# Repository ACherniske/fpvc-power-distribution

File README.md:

# FPVC Power Distribution Board

A 2-layer power distribution board designed in KiCad for the NFPA Fluid Powered Vehicle Challenge. Handles input fusing, load switching via MOSFETs, and regulated 5V/12V/24V outputs.

---

## Board Images

### Top and bottom layers

| Top layer | Bottom layer |
|---|---|
|  |  |

### Schematic

---

## Ordering from JLCPCB

### 1. Download the Gerber files

Download the latest Gerber files from the [Releases](../../releases) page as a `.zip` file. Do not unzip it — JLCPCB accepts the zip directly.

### 2. Upload to JLCPCB

1. Go to [jlcpcb.com](https://jlcpcb.com) and click **Order Now**
2. Click **Add Gerber File** and upload the `.zip`
3. JLCPCB will render a preview of the board — verify it looks correct before continuing

### 3. Configure the order options

Once uploaded, a list of fabrication options will appear. Set them as follows:

| Option | Value | Notes |
|---|---|---|
| **Base Material** | FR-4 | Standard PCB material |
| **Layers** | 2 | |
| **Dimensions** | Auto-detected | Verify against preview |
| **PCB Qty** | 5 (minimum) | Adjust as needed |
| **PCB Thickness** | 1.6mm | Standard |
| **PCB Color** | Your choice | Green is cheapest/fastest |
| **Silkscreen** | White | |
| **Surface Finish** | HASL (with lead) | Lead-free HASL also fine |
| **⚠️ Outer Copper Weight** | **2oz** | **Critical — must change from default** |
| **Via Covering** | Tented | |
| **Board Outline Tolerance** | ±0.2mm | Standard |
| **Confirm Production File** | No | |
| **Remove Order Number** | No | Yes adds ~$1.50 |

> **Why 2oz copper?** This board carries significant DC load currents through its power traces. 2oz copper (70µm) doubles the trace cross-sectional area compared to the default 1oz, reducing resistance and heat buildup. **Do not order with 1oz copper.**

### 4. Shipping & checkout

1. Click **Save to Cart**
2. Select your shipping method — **DHL Express** or **FedEx** typically arrive in 5–7 days to the US. Economy options are cheaper but can take 3–5 weeks
3. Complete checkout and pay

JLCPCB will send an email when the order moves to production and again when it ships.

---

## Bill of Materials

See [`fpvc-power-distribution-BOM.xlsx`](./documentation/fpvc-power-distribution-BOM.xlsx) for the full BOM. There is a mix of through-hole and surface-mount components. The 0805 package is hand-solderable or can be reflowed.

DigiKey links are provided in the BOM for all components that cannot be found in the Bucknell Maker-E Makerstock.

---

## License

Copyright 2026 Aiden Cherniske

Licensed under the Apache License, Version 2.0. See [`LICENSE`](./LICENSE) for the full text.

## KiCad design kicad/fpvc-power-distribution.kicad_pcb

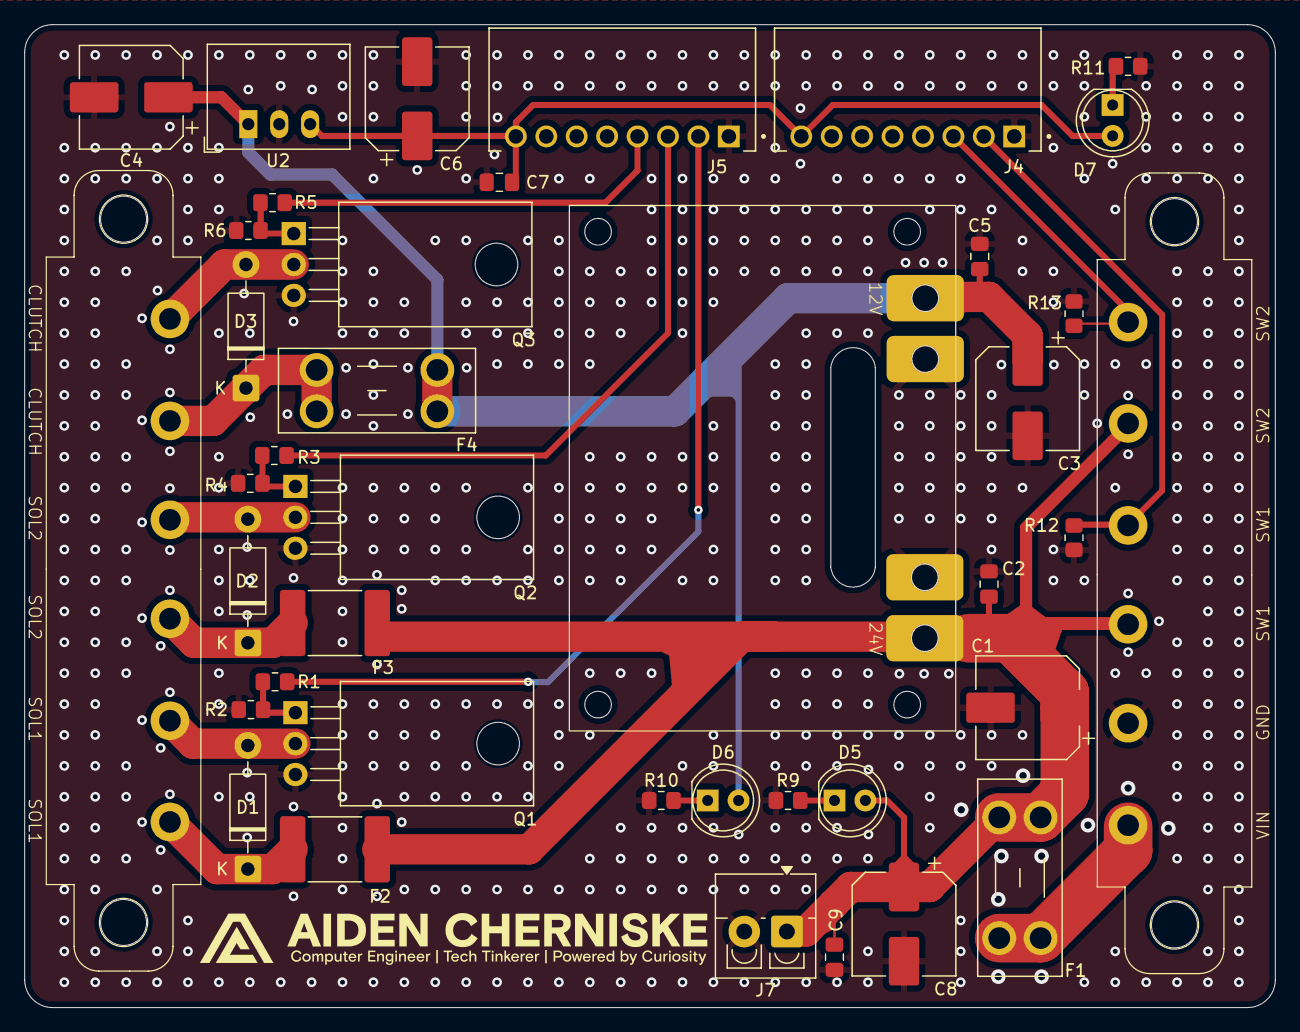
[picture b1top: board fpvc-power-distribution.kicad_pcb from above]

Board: 2 copper layers, 102.8 x 80.8 mm, 40 parts (0 on the bottom side), 22 nets.

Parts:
C1, C3, C4, C6, C8: 100uF; CP_Elec_8x6.2
C2, C5, C7, C9: 100nF; C_0805_2012Metric_Pad1.18x1.45mm_HandSolder
D1, D2, D3: 1N5819; D_DO-41_SOD81_P10.16mm_Horizontal
D5: 24V_Ind; LED_D5.0mm
D6: 12V_Ind; LED_D5.0mm
D7: 5V_Ind; LED_D5.0mm
F1: 15A Fuse; Fuseholder_Blade_Mini_Keystone_3568
F2, F3: 2A Polyfuse; Fuse_2920_7451Metric_Pad2.10x5.45mm_HandSolder
F4: 8A Fuse; Fuseholder_Blade_Mini_Keystone_3568
J4: PLC_In; PHOENIX_1881503
J5: PLC_Out; PHOENIX_1881503
J7: Vout_Screen; TerminalBlock_4Ucon_1x02_P3.50mm_Vertical
J9: GPIO; 8.26mm Pitch Beau PCB Terminal Strip
J10: Load Drivers; 8.26mm Pitch Beau PCB Terminal Strip
Q1, Q2, Q3: IRLB8314; TO-220-3_Horizontal_TabDown
R1, R3, R5: 220; R_0805_2012Metric_Pad1.20x1.40mm_HandSolder
R2, R4, R6, R12, R13: 10k; R_0805_2012Metric_Pad1.20x1.40mm_HandSolder
R9: 2.2k; R_0805_2012Metric_Pad1.20x1.40mm_HandSolder
R10: 1k; R_0805_2012Metric_Pad1.20x1.40mm_HandSolder
R11: 200; R_0805_2012Metric_Pad1.20x1.40mm_HandSolder
U1: D42V110F12
U2: R-78K 5.0-1.0; Converter_DCDC_RECOM_R-78E-0.5_THT

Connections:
24V: C1.1, C2.1, C8.1, C9.1, D5.2 (A), F1.2, F2.1, F3.1, J7.1, J9.2, J9.4, U1.1 (Vin)
+5V: C6.1, C7.1, D7.2 (A), J4.8, J5.8, U2.3 (OUT)
+12V: C3.1, C4.1, C5.1, D6.2 (A), F4.1, U1.3 (Vout), U2.1 (IN)
/C-G: Q3.1 (G), R5.2, R6.1
/Clu-1: D3.1 (K), F4.2, J10.5
/Clu-2: D3.2 (A), J10.6, Q3.2 (D)
/S1-G: Q1.1 (G), R1.2, R2.1
/S2-G: Q2.1 (G), R3.2, R4.1
/Sol1-1: D1.1 (K), F2.2, J10.1
/Sol1-2: D1.2 (A), J10.2, Q1.2 (D)
/Sol2-1: D2.1 (K), F3.2, J10.3
/Sol2-2: D2.2 (A), J10.4, Q2.2 (D)
GND: C1.2, C2.2, C3.2, C4.2, C5.2, C6.2, C7.2, C8.2, C9.2, J4.1, J5.1, J7.2, J9.5, Q1.3 (S), Q2.3 (S), Q3.3 (S), R2.2, R4.2, R6.2, R9.1, R10.1, R11.1, R12.2, R13.2, U1.2 (GND), U2.2 (GND)
unnamed: D5.1 (K), R9.2
unnamed: D6.1 (K), R10.2
unnamed: D7.1 (K), R11.2
PLC-C: J5.4, R5.1
PLC-S1: J5.2, R1.1
PLC-S2: J5.3, R3.1
PLC_SW1: J4.2, J9.3, R12.1
PLC_SW2: J4.3, J9.1, R13.1
VIN: F1.1, J9.6

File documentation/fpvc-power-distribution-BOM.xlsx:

FPVC Power Distribution — Bill of Materials
Qty | Designator | Val | Footprint | Link
5 | R2,R13,R4,R12,R6 | 10k | R_0805_2012Metric_Pad1.20x1.40mm_HandSolder | Maker-E Components
3 | D3,D1,D2 | 1N5819 | D_DO-41_SOD81_P10.16mm_Horizontal | https://www.digikey.com/en/products/detail/stmicroelectronic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
2 | F1, F4 | Various | Fuseholder_Blade_Mini_Keystone_3568 | https://www.digikey.com/en/products/detail/keystone-electron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
1 | F1 | 15A | Mini Blade Fuse | https://www.digikey.com/en/products/detail/littelfuse-inc/0M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
1 | F4 | 7.5A | Mini Blade Fuse | https://www.digikey.com/en/products/detail/littelfuse-inc/02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
5 | C4,C6,C3,C1,C8 | 100uF | CP_Elec_8x6.2 | https://www.digikey.com/en/products/detail/vishay-beyschlag-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
3 | Q3,Q1,Q2 | IRLB8314 | TO-220-3_Horizontal_TabDown | https://stock.maker.bucknell.edu/product/nmos-through-hole-3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
4 | C5,C2,C9,C7 | 0.1uF | C_0805_2012Metric_Pad1.18x1.45mm_HandSolder | Maker-E Components
1 | R9 | 2.2k | R_0805_2012Metric_Pad1.20x1.40mm_HandSolder | Maker-E Components
3 | D5, D6, D7 | Various | LED_D5.0mm | https://stock.maker.bucknell.edu/product/led-red-2/
3 | R3,R5,R1 | 220 | R_0805_2012Metric_Pad1.20x1.40mm_HandSolder | Maker-E Components
1 | R11 | 200 | R_0805_2012Metric_Pad1.20x1.40mm_HandSolder | Maker-E Components
2 | F3,F2 | 2A Polyfuse | Fuse_2920_7451Metric_Pad2.10x5.45mm_HandSolder | https://www.digikey.com/en/products/detail/bourns-inc/MF-LSM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
1 | R10 | 1k | R_0805_2012Metric_Pad1.20x1.40mm_HandSolder | Maker-E Components
1 | U2 | R-78K 5.0-1.0 | Converter_DCDC_RECOM_R-78E-0.5_THT | https://stock.maker.bucknell.edu/product/dc-dc-converter-5-v-1-a/
1 | J7 | Vout_Screen | TerminalBlock_4Ucon_1x02_P3.50mm_Vertical | https://stock.maker.bucknell.edu/product/terminal-blocks-2/
2 | J4, J5 | Various | PHOENIX_1881503 | https://www.digikey.com/en/products/detail/phoenix-contact/1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
2 | J4, J5 | Various | PHOENIX_1881383 | https://www.digikey.com/en/products/detail/phoenix-contact/1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
2 | J9, J10 | Various | 8.26mm Pitch Beau PCB Terminal Strip | https://www.digikey.in/en/products/detail/molex/0387006106/3315660

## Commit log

2026-03-15 chore: Create kicad 9 project
2026-03-15 feat: Plan mosfet based solenoid and clutch actuation
2026-03-15 feat: Create voltage regulator symbol and schematic
2026-03-15 feat: Add proper regulator fault detection and power indication
2026-03-19 feat: Add 5V DC/DC converter for PLC
2026-03-19 style: Clean up schematic and add labels
2026-03-19 style: Complete schematic formatting
2026-03-24 feat: Update schematic with GPIO connectors
2026-03-24 fix: Add decoupling caps to screen power connector
2026-03-24 style: Fix formatting in I/O section
2026-03-24 feat: Add custom footprints
2026-03-24 feat: Fix annotations and footprint assignments
2026-03-24 feat: Finish PCB revision 1
2026-03-24 feat: Generate stitching vias
2026-03-24 fix: Correct 24V trace angle
2026-03-24 feat: Update silkscreen
2026-03-25 feat: Update 3d models
2026-03-25 fix: Replace 2.54mm pitch pin header with 3.5mm terminal block for screen power connections
2026-03-25 style: Update pcb editor information and clean up file
2026-03-26 feat: Add BOM with digikey links and makerstock components
2026-03-26 feat: Generate fabrication outputs
2026-03-26 chore: Update License
2026-03-26 feat: Add fabrication output zip file
2026-03-26 docs: Update README with detailed ordering instructions
2026-03-26 docs: Remove D42V110F12 Voltage Regulator Pin Summary documentation
2026-03-26 docs: Add DESIGN_DECISIONS.md with PCB design rationale and decisions
2026-03-26 docs: Update net_colors and plot_directory in KiCad project file
2026-03-26 docs: Add schematic and pcb images
2026-03-26 docs: Add board images and schematic to README
2026-03-26 docs: Add power distribution schematic PDF to documentation
2026-03-26 fix: Update README

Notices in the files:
README.md:
License: Apache 2.0
